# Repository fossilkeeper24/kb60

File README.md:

# kb60

> just another custom 60% keyboard

I didn't like having a numpad on my keyboard because it just collects dust as I never use the numpad. I also like having super easy to access media control. So I thought yeah why not let's make our own keyboard :3 While having the most minor changes to a 60% ISO layout keyboard, it's different enough to warrant its own project.

## Some pictures

## BOM

|Name          |Link                                                                                                                                                                                                                                                                                                                                                                                                                                                                                                                                                                                                                                                                                                                                                                         |price ($)|Notes                                              |
|--------------|-----------------------------------------------------------------------------------------------------------------------------------------------------------------------------------------------------------------------------------------------------------------------------------------------------------------------------------------------------------------------------------------------------------------------------------------------------------------------------------------------------------------------------------------------------------------------------------------------------------------------------------------------------------------------------------------------------------------------------------------------------------------------------|---------|---------------------------------------------------|
|rasp pi pico  |https://www.aliexpress.com/item/1005003753933847.html |2.40   |                                                   |
|rotary encoder |https://www.aliexpress.com/item/1005005983134515.html |2.59    | 15mm length                                       |
|stabilizers   |https://www.aliexpress.com/item/1005001632672798.html |17.89   |choose ones that go with whatever switches i choose|
|switches      |https://www.aliexpress.com/item/1005007665996795.html                                                                                                          |14.68*2   |                                                   |
|diodes        |https://www.aliexpress.com/item/2025724181.html|1.91    |                                                   |
|keycaps       |https://www.aliexpress.com/item/1005008714429564.html |33.30   |142 keys                                           |
|m3x12 screws  |https://www.aliexpress.com/item/32510989714.html |1.58    |                                                   |
|m3 heatset    |https://www.aliexpress.com/item/1005006838108683.html |1.99    |L4 4.2mm                                                  |
|PLA           |print legion goats |         |                                                   |
|PCB           |JLC PCB |31.85   |there are many coupons that i could use            |
|TOTAL         | |122.87   |                                                   |

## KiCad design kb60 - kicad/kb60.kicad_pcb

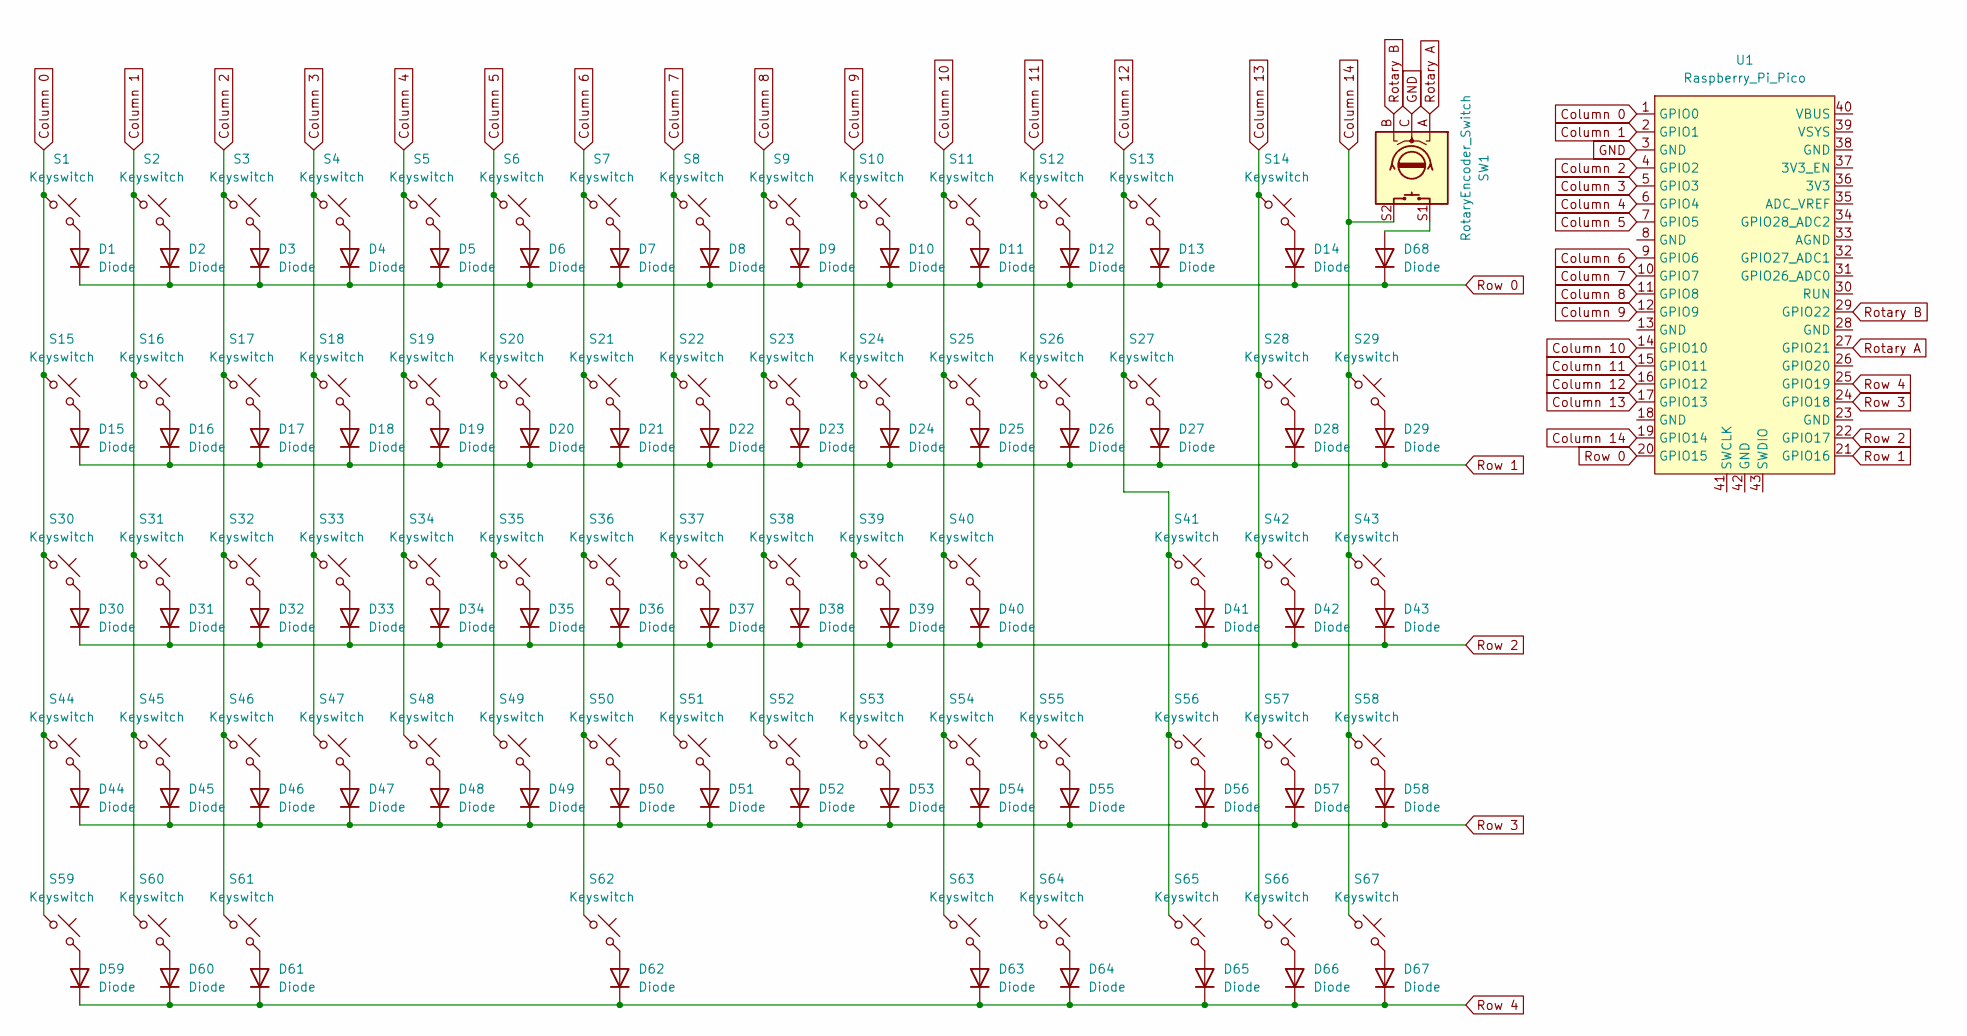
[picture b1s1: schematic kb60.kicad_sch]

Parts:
D1, D2, D3, D4, D5, D6, D7, D8, D9, D10, D11, D12, D13, D14, D15, D16, D17, D18, D19, D20, D21, D22, D23, D24, D25, D26, D27, D28, D29, D30, D31, D32, D33, D34, D35, D36, D37, D38, D39, D40, D41, D42, D43, D44, D45, D46, D47, D48, D49, D50, D51, D52, D53, D54, D55, D56, D57, D58, D59, D60, D61, D62, D63, D64, D65, D66, D67, D68: Diode; Diode_DO-35
S1, S2, S3, S4, S5, S6, S7, S8, S9, S10, S11, S12, S13, S14, S15, S16, S17, S18, S19, S20, S21, S22, S23, S24, S25, S26, S27, S28, S29, S30, S31, S32, S33, S34, S35, S36, S37, S38, S39, S40, S41, S42, S43, S44, S45, S46, S47, S48, S49, S50, S51, S52, S53, S54, S55, S56, S57, S58, S59, S60, S61, S62, S63, S64, S65, S66, S67: Keyswitch; MX_PCB_1.00u
SW1: RotaryEncoder_Switch; RotaryEncoder_Alps_EC12E-Switch_Vertical_H20mm
U1: Raspberry_Pi_Pico

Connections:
Column 0: S1.1, S15.1, S30.1, S44.1, S59.1, U1.1 (GPIO0)
Column 1: S2.1, S16.1, S31.1, S45.1, S60.1, U1.2 (GPIO1)
Column 2: S3.1, S17.1, S32.1, S46.1, S61.1, U1.4 (GPIO2)
Column 3: S4.1, S18.1, S33.1, S47.1, U1.5 (GPIO3)
Column 4: S5.1, S19.1, S34.1, S48.1, U1.6 (GPIO4)
Column 5: S6.1, S20.1, S35.1, S49.1, U1.7 (GPIO5)
Column 6: S7.1, S21.1, S36.1, S50.1, S62.1, U1.9 (GPIO6)
Column 7: S8.1, S22.1, S37.1, S51.1, U1.10 (GPIO7)
Column 8: S9.1, S23.1, S38.1, S52.1, U1.11 (GPIO8)
Column 9: S10.1, S24.1, S39.1, S53.1, U1.12 (GPIO9)
Column 10: S11.1, S25.1, S40.1, S54.1, S63.1, U1.14 (GPIO10)
Column 11: S12.1, S26.1, S55.1, S64.1, U1.15 (GPIO11)
Column 12: S13.1, S27.1, S41.1, S56.1, S65.1, U1.16 (GPIO12)
Column 13: S14.1, S28.1, S42.1, S57.1, S66.1, U1.17 (GPIO13)
Column 14: S29.1, S43.1, S58.1, S67.1, SW1.S2, U1.19 (GPIO14)
GND: SW1.C, U1.3 (GND)
unnamed: D1.2 (A), S1.2
unnamed: D2.2 (A), S2.2
unnamed: D3.2 (A), S3.2
unnamed: D4.2 (A), S4.2
unnamed: D5.2 (A), S5.2
unnamed: D6.2 (A), S6.2
unnamed: D7.2 (A), S7.2
unnamed: D8.2 (A), S8.2
unnamed: D9.2 (A), S9.2
unnamed: D10.2 (A), S10.2
unnamed: D11.2 (A), S11.2
unnamed: D12.2 (A), S12.2
unnamed: D13.2 (A), S13.2
unnamed: D14.2 (A), S14.2
unnamed: D15.2 (A), S15.2
unnamed: D16.2 (A), S16.2
unnamed: D17.2 (A), S17.2
unnamed: D18.2 (A), S18.2
unnamed: D19.2 (A), S19.2
unnamed: D20.2 (A), S20.2
unnamed: D21.2 (A), S21.2
unnamed: D22.2 (A), S22.2
unnamed: D23.2 (A), S23.2
unnamed: D24.2 (A), S24.2
unnamed: D25.2 (A), S25.2
unnamed: D26.2 (A), S26.2
unnamed: D27.2 (A), S27.2
unnamed: D28.2 (A), S28.2
unnamed: D29.2 (A), S29.2
unnamed: D30.2 (A), S30.2
unnamed: D31.2 (A), S31.2
unnamed: D32.2 (A), S32.2
unnamed: D33.2 (A), S33.2
unnamed: D34.2 (A), S34.2
unnamed: D35.2 (A), S35.2
unnamed: D36.2 (A), S36.2
unnamed: D37.2 (A), S37.2
unnamed: D38.2 (A), S38.2
unnamed: D39.2 (A), S39.2
unnamed: D40.2 (A), S40.2
unnamed: D41.2 (A), S41.2
unnamed: D42.2 (A), S42.2
unnamed: D43.2 (A), S43.2
unnamed: D44.2 (A), S44.2
unnamed: D45.2 (A), S45.2
unnamed: D46.2 (A), S46.2
unnamed: D47.2 (A), S47.2
unnamed: D48.2 (A), S48.2
unnamed: D49.2 (A), S49.2
unnamed: D50.2 (A), S50.2
unnamed: D51.2 (A), S51.2
unnamed: D52.2 (A), S52.2
unnamed: D53.2 (A), S53.2
unnamed: D54.2 (A), S54.2
unnamed: D55.2 (A), S55.2
unnamed: D56.2 (A), S56.2
unnamed: D57.2 (A), S57.2
unnamed: D58.2 (A), S58.2
unnamed: D59.2 (A), S59.2
unnamed: D60.2 (A), S60.2
unnamed: D61.2 (A), S61.2
unnamed: D62.2 (A), S62.2
unnamed: D63.2 (A), S63.2
unnamed: D64.2 (A), S64.2
unnamed: D65.2 (A), S65.2
unnamed: D66.2 (A), S66.2
unnamed: D67.2 (A), S67.2
unnamed: D68.2 (A), SW1.S1
Rotary A: SW1.A, U1.27 (GPIO21)
Rotary B: SW1.B, U1.29 (GPIO22)
Row 0: D1.1 (K), D2.1 (K), D3.1 (K), D4.1 (K), D5.1 (K), D6.1 (K), D7.1 (K), D8.1 (K), D9.1 (K), D10.1 (K), D11.1 (K), D12.1 (K), D13.1 (K), D14.1 (K), D68.1 (K), U1.20 (GPIO15)
Row 1: D15.1 (K), D16.1 (K), D17.1 (K), D18.1 (K), D19.1 (K), D20.1 (K), D21.1 (K), D22.1 (K), D23.1 (K), D24.1 (K), D25.1 (K), D26.1 (K), D27.1 (K), D28.1 (K), D29.1 (K), U1.21 (GPIO16)
Row 2: D30.1 (K), D31.1 (K), D32.1 (K), D33.1 (K), D34.1 (K), D35.1 (K), D36.1 (K), D37.1 (K), D38.1 (K), D39.1 (K), D40.1 (K), D41.1 (K), D42.1 (K), D43.1 (K), U1.22 (GPIO17)
Row 3: D44.1 (K), D45.1 (K), D46.1 (K), D47.1 (K), D48.1 (K), D49.1 (K), D50.1 (K), D51.1 (K), D52.1 (K), D53.1 (K), D54.1 (K), D55.1 (K), D56.1 (K), D57.1 (K), D58.1 (K), U1.24 (GPIO18)
Row 4: D59.1 (K), D60.1 (K), D61.1 (K), D62.1 (K), D63.1 (K), D64.1 (K), D65.1 (K), D66.1 (K), D67.1 (K), U1.25 (GPIO19)

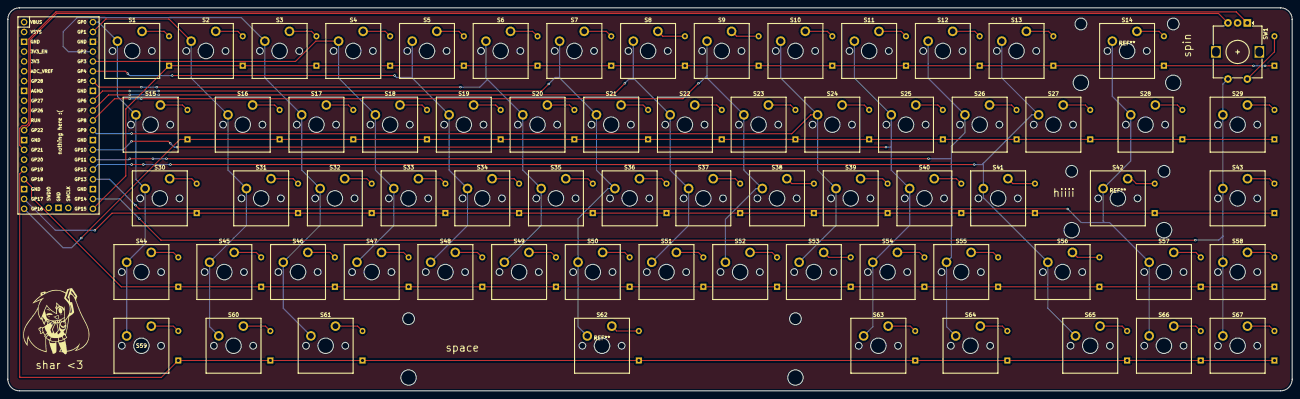
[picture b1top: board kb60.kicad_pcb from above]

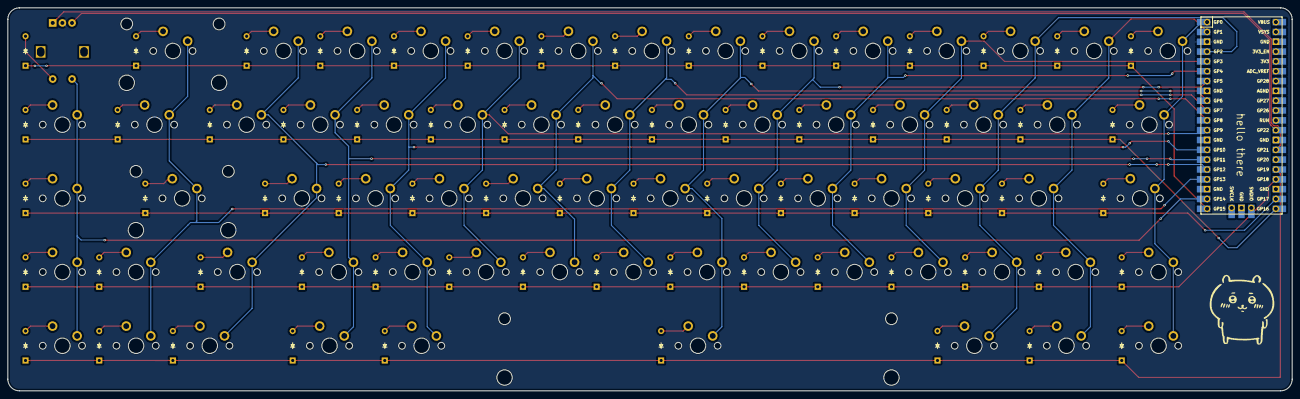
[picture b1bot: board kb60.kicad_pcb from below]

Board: 2 copper layers, 332.0 x 99.0 mm, 137 parts (69 on the bottom side), 91 nets.

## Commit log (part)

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2025-11-11 initialise project
2025-11-11 Add submodules
2025-11-11 Add correct submodules
2025-11-11 Delete OPL Kicad library
    I dont need it
2025-11-12 i was wrong yesterday
    i did not need these submodules
2025-11-16 added missing 3d models of components
2025-11-23 made schematic for led matrix
    also imported scottokeebs library
2025-11-29 completed schematic
2025-11-29 started pcb design
    placed keys in rough places
2025-12-02 added rotary encoder to switch matrix
    as it has a switch as well
    also added my keyboard layout that i wanted as a guideline for pcb placement
2025-12-02 pcb layout mostly done and 3d models added
2025-12-02 finished pcb placements
2025-12-23 finished routing pcb
2025-12-24 added ground fill and prod files
2025-12-24 added plate dxf file
    from plate generator
2025-12-28 made the pcb a lil smaller
    and moved some components
2026-01-11 upload kmk files
2026-01-17 added function layer
2026-01-17 add a lil more to readme
2026-03-12 Added BOM
2026-03-14 added the fusion cad
2026-03-14 tinkering with how the readme looks
2026-03-14 added pics to readme
2026-03-14 add bom.csv
2026-03-14 reorganise folders
2026-03-14 renamed file for clarity
2026-03-14 add stabilizers to pcb
2026-03-15 fixed cad errors
    added tolerance to where the pcb goes. split the case so that it is easier to print. fixed alignment errors
2026-03-16 centered pcb in kicad
2026-03-17 changed link to diodes
    because original link is no longer available
2026-03-17 replaced pcb pic with updated ver
2026-03-17 update bom links
2026-03-17 made bom notes more specific
2026-03-17 fix bom prices
2026-03-18 removed 90 degree traces
    was given feedback to as it is not best practice
